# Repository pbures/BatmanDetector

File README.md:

# BatmanDetector

The project based on sonic SR04 sensor.

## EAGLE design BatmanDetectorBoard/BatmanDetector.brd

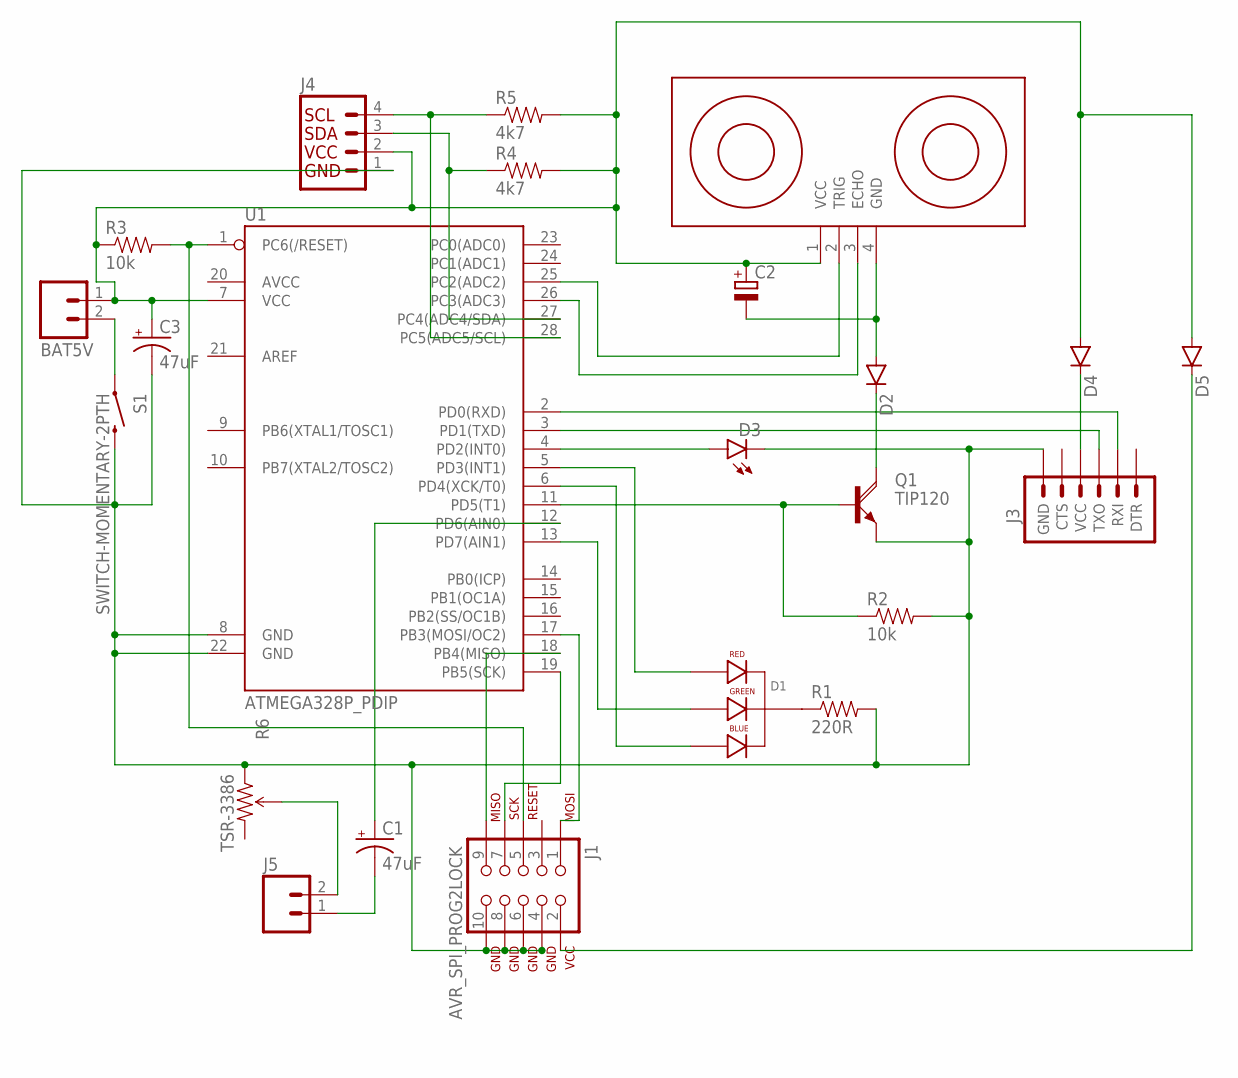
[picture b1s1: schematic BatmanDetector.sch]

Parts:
BAT5V: M02JST-PTH-VERT; JST-2-PTH-VERT
C1, C3: 47uF; CPOL-RADIAL-10UF-25V
C2: CPOL-EUE15-5AXIAL; E15-5
D1: LED-RGB-CC-THRUDIFFUSE; LED-RGB-THRU
D2, D4, D5: DIODE1N4148; DIODE-1N4148
D3: LED-3MM-NO_SILK; LED3MM-NS
J1: AVR_SPI_PROG2LOCK; 2X5-SHROUDED_LOCK
J3: ARDUINO_SERIAL_PROGRAMLONGPADS; 1X06_LONGPADS
J4: I2C_STANDARD_NO_SILK; 1X04_NO_SILK
J5: M02PTH3; 1X02_LONGPADS
Q1: TIP120; TO220AH
R1: 220R; AXIAL-0.3
R2, R3: 10k; AXIAL-0.3
R4, R5: 4k7; AXIAL-0.3
R6: TSR-3386; 3386U
S1: SWITCH-MOMENTARY-2PTH; TACTILE-PTH
U1: ATMEGA328P_PDIP; DIL28-3
U$1: ULTRASONIC-HC-SR04#V

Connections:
unnamed: D1.1 (RED_CATHODE), U1.5 (PD3(INT1))
unnamed: J1.1 (MOSI), U1.17 (PB3(MOSI/OC2))
unnamed: J1.7 (SCK), U1.19 (PB5(SCK))
unnamed: J3.2 (RXI), U1.2 (PD0(RXD))
unnamed: J3.3 (TXO), U1.3 (PD1(TXD))
unnamed: D3.A, U1.4 (PD2(INT0))
unnamed: Q1.B, R2.P$1 (1), U1.11 (PD5(T1))
unnamed: C2.-, D2.A, U$1.4 (GND)
unnamed: D2.C, Q1.C
unnamed: D1.4 (BLUE_CATHODE), U1.6 (PD4(XCK/T0))
unnamed: D1.3 (GREEN_CATHODE), U1.13 (PD7(AIN1))
unnamed: D1.2 (CATHODE), R1.P$1 (1)
unnamed: U1.25 (PC2(ADC2)), U$1.2 (TRIG)
unnamed: J5.2, R6.2 (WIPER)
unnamed: J1.5 (RESET), R3.P$2 (2), U1.1 (PC6(/RESET))
unnamed: J4.3, R4.P$1 (1), U1.27 (PC4(ADC4/SDA))
unnamed: U1.26 (PC3(ADC3)), U$1.3 (ECHO)
unnamed: J4.4, R5.P$1 (1), U1.28 (PC5(ADC5/SCL))
unnamed: D4.C, J3.4 (VCC)
unnamed: D5.C, J1.2 (VCC)
unnamed: C1.2 (-), J5.1
unnamed: C1.1 (+), U1.12 (PD6(AIN0))
unnamed: J1.9 (MISO), U1.18 (PB4(MISO))
unnamed: C3.2 (-), D3.K (C), J1.4 (GND), J1.6 (GND), J1.8 (GND), J1.10 (GND), J3.6 (GND), J4.1, Q1.E, R1.P$2 (2), R2.P$2 (2), R6.1 (CCW), S1.3 (2), U1.8 (GND), U1.22 (GND)
unnamed: BAT5V.2, S1.1
unnamed: BAT5V.1, C2.+, C3.1 (+), D4.A, D5.A, J4.2, R3.P$1 (1), R4.P$2 (2), R5.P$2 (2), U1.7 (VCC), U$1.1 (VCC)

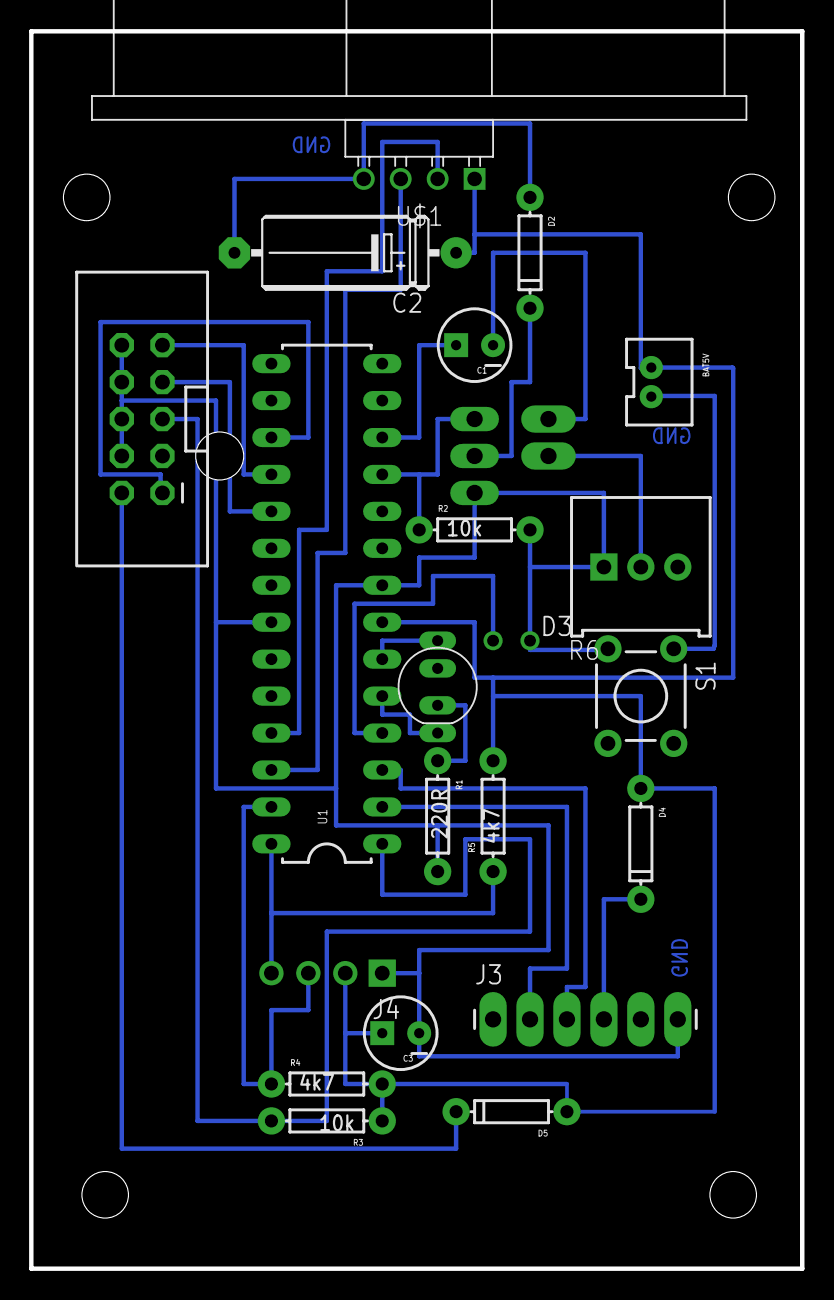
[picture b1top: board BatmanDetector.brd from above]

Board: 2 copper layers, 53.0 x 85.1 mm, 23 parts (1 on the bottom side), 26 nets.

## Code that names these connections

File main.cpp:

#include <avr/io.h>
#include <util/delay.h>
#include <avr/interrupt.h>

#define TRIG_DDR    DDRC           // Trigger Port
#define TRIG_PORT   PORTC
#define TRIG_PIN    PINC
#define TRIG_BIT    PC2             // Trigger Pin

#define ECHO_DDR    DDRC            // Echo Port
#define ECHO_PORT   PORTC
#define ECHO_PIN    PINC
#define ECHO_BIT    PC3             // Echo Pin

#define EPWR_DDR	DDRD            // TIP120 power switching mosfet.
#define EPWR_PORT 	PORTD
#define	EPWR_PIN	PIND
#define EPWR_BIT	PD5

#define ECHO_LED_DDR    DDRD	// LED Pin
#define ECHO_LED_PORT	PORTD
#define ECHO_LED_PIN	PIND
#define ECHO_LED_BIT	PD2

/* Define pins for debug LED */
#define RED_DDR     DDRD
#define RED_PORT	PORTD
#define RED_PIN		PIND
#define RED_BIT		PD3

#define BLUE_DDR    DDRD
#define BLUE_PORT	PORTD
#define BLUE_PIN	PIND
#define BLUE_BIT	PD4

#define GRN_DDR     DDRD
#define GRN_PORT	PORTD
#define GRN_PIN		PIND
#define GRN_BIT		PD7

#define SPKR_DDR 	DDRD
#define SPKR_PORT 	PORTD
#define SPKR_PIN 	PIND
#define SPKR_BIT 	PD6

#define SPEED_OF_SOUND  343                                           /* meters in second. */
#define MAX_SONAR_RANGE 10                                            /* meters */
#define SONAR_TIMEOUT_CNTMAX ((F_CPU*MAX_SONAR_RANGE)/SPEED_OF_SOUND) /* range/speed = time until timeout. */
/* time * F_CPU = number of ticks until timeout */

#define DELAY_BETWEEN_DETECTION_MS 100  /* Time between measurements */
#define TIMER_MAX 65535                 /* 65535 for 16 bit timer, Timer1 is 16 bit one */
#define DISTANCE_SIGNAL_MAX_CM 60       /* Above this distance, it is considered as without obstacle. */
#define DISTANCE_SIGNAL_MIN_CM 20       /* Below this distance, the signal pitch is maxed out. */

#define TRIG_ERROR -1
#define ECHO_ERROR -2

#define CYCLES_PER_US (F_CPU/1000000)// instructions per microsecond


#define SET_INPUT_MODE(ddr,bit) ddr &= ~(1<<bit)
#define SET_OUTPUT_MODE(ddr,bit) ddr |= (1<<bit)
#define SET_HIGH(port,bit) port |= (1<<bit)
#define SET_LOW(port,bit) port &= ~(1<<bit)

#define SET_LOW_AND_DELAY(port,bit,delay) port &= ~(1<<bit);_delay_us(delay)
#define SET_HIGH_AND_DELAY(port,bit,delay) port |= (1<<bit);_delay_us(delay)

#define TICKS_TO_CM(ticks) (ticks/(((10000*2)/SPEED_OF_SOUND) * CYCLES_PER_US))

volatile uint32_t timerOverflowCnt = 0;
volatile uint32_t trigCnt = 0;

void initSonar() {

	SET_INPUT_MODE(ECHO_DDR, ECHO_BIT);

	SET_OUTPUT_MODE(TRIG_DDR, TRIG_BIT);
	SET_OUTPUT_MODE(ECHO_LED_DDR, ECHO_LED_BIT);
	SET_OUTPUT_MODE(RED_DDR, ECHO_LED_BIT);
	SET_OUTPUT_MODE(GRN_DDR, GRN_BIT);
	SET_OUTPUT_MODE(EPWR_DDR, EPWR_BIT);

	SET_HIGH(EPWR_PORT, EPWR_BIT);
}

void triggerSonar() {
	SET_LOW_AND_DELAY(TRIG_PORT, TRIG_BIT,1); /* First clear the pin */
	SET_HIGH_AND_DELAY(TRIG_PORT, TRIG_BIT,12); /* Send high impulse for sth over 10 us */
	SET_LOW_AND_DELAY(TRIG_PORT, TRIG_BIT,1); /* Set back to low */
}

/* The cheap sonar sensors get stuck when no echo is received. If timeout is reached, reset the device
 * by powering down for 10ms.
 */
void rebootSonar() {
	SET_LOW_AND_DELAY(EPWR_PORT, EPWR_BIT,200);
	SET_HIGH(EPWR_PORT, EPWR_BIT);
}

/* Count number of timer overflows, this tells us how many cycles passed */
ISR(TIMER1_OVF_vect) {
	timerOverflowCnt++;
	TCNT1 = 0;
}

int16_t readSonar() {

//	init_sonar();                       // Setup pins and ports
	triggerSonar();                    // send a 10us high pulse

	while (!(ECHO_PIN & (1 << ECHO_BIT))) {
		trigCnt++;
		uint32_t max_response_time = SONAR_TIMEOUT_CNTMAX;
		if (trigCnt > max_response_time) {
			return TRIG_ERROR; /* Echo signal was never sent */
		}
	}

	trigCnt = 0;

	/* Reset the Timer1, start without prescaler and enable overflow interrupt */
	TCNT1 = 0;
	TCCR1B |= (1 << CS10);
	TIMSK1 |= (1 << TOIE1);
	timerOverflowCnt = 0;
	sei();

	/* Wait for signal on echo pin */
	while ((ECHO_PIN & (1 << ECHO_BIT))) {
		if (((timerOverflowCnt * TIMER_MAX) + TCNT1) > SONAR_TIMEOUT_CNTMAX) {
			return ECHO_ERROR;          /* We reached timeout, echo is still up */
		}
	};

	TCCR1B = 0x00;                      // stop 16 bit timer with no prescaler
	cli();

	return TICKS_TO_CM((timerOverflowCnt * TIMER_MAX) + TCNT1);
}

void speakerOnByDistance(uint16_t distanceCm) {
	/* Distance is 0 .. 150, need to map to 33 .. 255*/
	/* 30 cm or lower is the highest pitch anyway */

	uint16_t distance =
			(distanceCm < DISTANCE_SIGNAL_MIN_CM) ?
					0 : distanceCm - DISTANCE_SIGNAL_MIN_CM;
	uint16_t wavelength = 33
			+ (distance * 222
					/ (DISTANCE_SIGNAL_MAX_CM - DISTANCE_SIGNAL_MIN_CM));

	OCR0A = (wavelength > 255) ? 255 : wavelength;
	SPKR_DDR |= (1 << SPKR_BIT);
}

void speakerOff() {
	SPKR_DDR &= ~(1 << SPKR_BIT);
}

void initSpeaker() {
	speakerOff();
	TCCR0A |= (1 << WGM01);  /* CTC Mode */
	TCCR0A |= (1 << COM0A0); /* Toggle PD6 on cycle through */
	TCCR0B |= ((1 << CS00) | (1 << CS01)); /* Prescaler to 64 */
}

void debugLedsBlink() {
	SET_HIGH_AND_DELAY(RED_PORT, RED_BIT, 500);
	SET_LOW(RED_PORT, RED_BIT);
	SET_HIGH_AND_DELAY(BLUE_PORT, BLUE_BIT, 500);
	SET_LOW(BLUE_PORT, BLUE_BIT);
	SET_HIGH_AND_DELAY(GRN_PORT, GRN_BIT, 500);
	SET_LOW(GRN_PORT, GRN_BIT);
}

int main() {
	int16_t distanceCm = 0;
	initSonar();
	initSpeaker();
	debugLedsBlink();

	while (1) {
		distanceCm = readSonar();
		if (distanceCm == TRIG_ERROR) {
			speakerOff();
			SET_LOW(BLUE_PORT, BLUE_BIT);
			SET_LOW(RED_PORT, RED_BIT);
			SET_HIGH(GRN_PORT, GRN_BIT);
			_delay_ms(DELAY_BETWEEN_DETECTION_MS);
		} else if (distanceCm == ECHO_ERROR) {
			speakerOff();
			SET_LOW(ECHO_LED_PORT, ECHO_LED_BIT);
			SET_LOW(BLUE_PORT, BLUE_BIT);
			SET_LOW(GRN_PORT, GRN_BIT);
			SET_HIGH(RED_PORT, RED_BIT);

			rebootSonar();
		} else {
			SET_HIGH(BLUE_PORT, BLUE_BIT);
			SET_LOW(RED_PORT, RED_BIT);
			SET_LOW(GRN_PORT, GRN_BIT);
			if (distanceCm < DISTANCE_SIGNAL_MAX_CM) {
				speakerOnByDistance(distanceCm);
				SET_HIGH(ECHO_LED_PORT, ECHO_LED_BIT);
			} else {
				speakerOff();
				SET_LOW(ECHO_LED_PORT, ECHO_LED_BIT);
			}
			_delay_ms(DELAY_BETWEEN_DETECTION_MS);
		}
	}
	return 0;
}

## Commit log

2016-09-16 Initial project commit of a first prototype.
2016-09-16 Added board schematics
2016-10-11 Spaces added in the macro definition.

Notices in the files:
parts and their libraries:
SparkFun-Passives: Licensing: Creative Commons ShareAlike 4.0 International - https://creativecommons.org/licenses/by-sa/4.0
diy-modules: Released under the Creative Commons Attribution 4.0 International License: http://creativecommons.org/licenses/by/4.0
